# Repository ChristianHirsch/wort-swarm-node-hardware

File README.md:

# wort-swarm-node-hardware

This piece of hardware consists of a ICM-20948 9-axis inertial measurement unit (IMU), a Si705x digital temperature sensor, a nRF52840 system on chip (SoC) and battery management.

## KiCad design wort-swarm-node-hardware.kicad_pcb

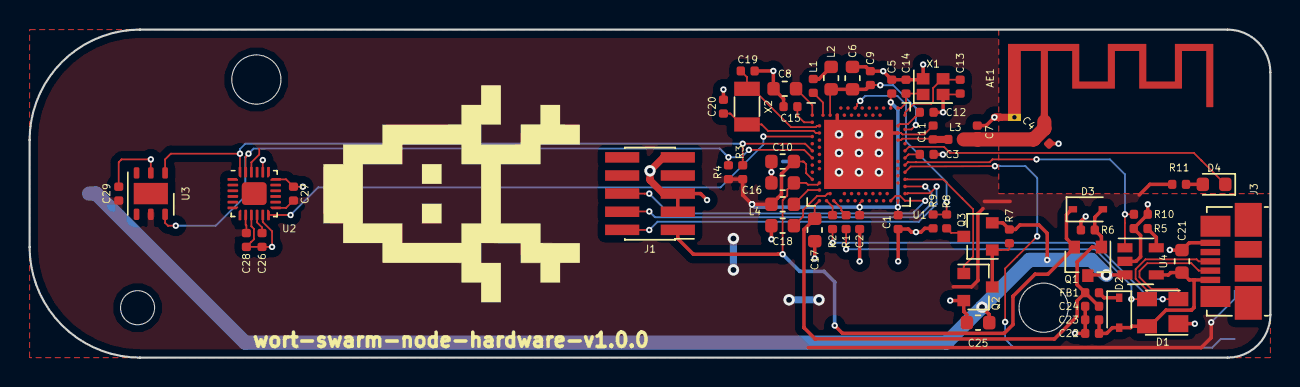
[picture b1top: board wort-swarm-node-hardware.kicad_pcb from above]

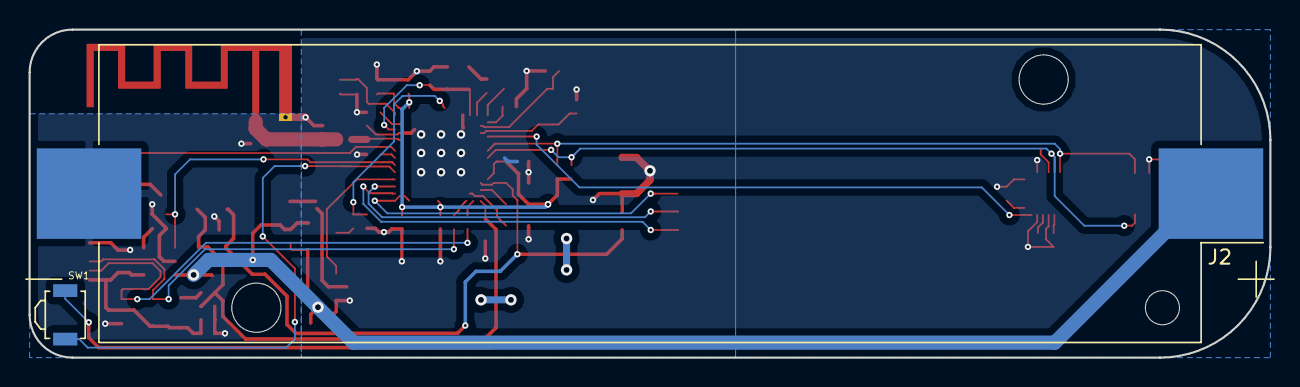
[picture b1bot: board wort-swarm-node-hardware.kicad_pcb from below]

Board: 2 copper layers, 87.0 x 23.0 mm, 63 parts (2 on the bottom side), 41 nets.

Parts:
AE1: Antenna_Shield; Texas_SWRA117D_2.4GHz_Right
C1, C2, C5, C15, C22, C24, C26, C27, C28, C29: 100n; C_0402_1005Metric
C3: 820p; C_0402_1005Metric
C4: N.C.; C_0402_1005Metric
C6, C8: 1u; C_0603_1608Metric
C7: 0.5p; C_0402_1005Metric
C9: 47n; C_0402_1005Metric
C10, C16, C17, C18, C25: 4.7u; C_0603_1608Metric
C11: 0.8p; C_0402_1005Metric
C12: 100p; C_0402_1005Metric
C13, C14, C19, C20: 12p; C_0402_1005Metric
C21: 10u; C_0603_1608Metric
C23: 10n; C_0402_1005Metric
D1: PRTR5V0U2X; SOT-143
D2, D3: BAT20J; D_SOD-323
D4: LED; LED_0603_1608Metric
FB1: 120R/0,55A; L_0402_1005Metric
J1: Conn_ARM_JTAG_SWD_10; PinHeader_2x05_P1.27mm_Vertical_SMD
J2: BATT_CONN; BatteryHolder_Keystone_1042_1x18650
J3: USB_B_Micro; USB_Micro-B_Molex_47346-0001
L1: 15n; L_0402_1005Metric
L2, L4: 10u; L_0603_1608Metric
L3: 3.9n, 5%; L_0402_1005Metric
Q1, Q3: DMP3099L-13; SOT-23
Q2: Q_NMOS_GSD; SOT-23
R1, R2: 0; R_0402_1005Metric
R3, R4, R6, R7, R10: 10k; R_0402_1005Metric
R5, R8: 3.3k; R_0402_1005Metric
R9: 8.2k; R_0402_1005Metric
R11: 220; R_0402_1005Metric
SW1: SW_Push; SW_SPST_B3U-3000P
U1: nRF52840; Nordic_AQFN-73-1EP_7x7mm_P0.5mm
U2: ICM-20948; QFN-24-1EP_3x3mm_P0.4mm_EP1.75x1.6mm
U3: Si7053-A20; DFN-6-1EP_3x3mm_P1mm_EP1.5x2.4mm
U4: MCP73812T-420I-OT; SOT-23-5
X1: 32MHz, 8pF; Crystal_SMD_2016-4Pin_2.0x1.6mm
X2: 32,768kHz, 9pF; Crystal_SMD_3215-2Pin_3.2x1.5mm

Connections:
+BATT: C25.1, J2.1, Q1.3, Q3.2, R7.1, U4.3
/ANT: C11.1, L3.2, U1.H23
/BATT_CHRG_EN: R10.1, U1.R24, U4.1
/BATT_V: R8.2, R9.1, U1.A12
/BATT_V_EN: Q2.1, U1.W24
/D+: R1.1, U1.AD6
/D-: R2.2, U1.AD4
/DCC: L1.1, U1.B3
/DCCH: L4.2, U1.AB2
/DEC1: C15.1, U1.C1
/DEC3: C12.1, U1.D23
/DEC4: C6.1, C9.1, L2.2, U1.B5, U1.E24
/DEC5: C3.1, U1.N24
/DECUSB: C18.1, U1.AC5
/ICM-20948_INT: U1.G1, U2.12
/LED: D4.1, U1.L24
/SCL: R4.2, U1.N1, U2.23, U3.6
/SDA: R3.2, U1.L1, U2.24, U3.1
/SWDCLK: J1.4, U1.AA24
/SWDIO: J1.2, U1.AC24
/SWO: J1.6, U1.AD22
/XC1: C13.2, U1.B24, X1.3
/XC2: C14.2, U1.A23, X1.1
/XL1: C19.2, U1.D2, X2.2
/XL2: C20.2, U1.F2, X2.1
/wort-swarm-node-hardware-components/V_USB: C21.1, C22.1, C23.1, D1.4, D2.2, J3.1, U4.4
GND: AE1.2, C1.2, C2.2, C3.2, C4.2, C5.2, C6.2, C7.2, C8.2, C9.2, C10.2, C11.2, C12.2, C13.1, C14.1, C15.2, C16.2, C17.2, C18.2, C19.1, C20.1, C21.2, C22.2, C23.2, C24.2, C25.2, C26.2, C27.2, C28.2, C29.2, D1.1, J1.3, J1.5, J1.9, J2.2, J3.5, Q2.2, R5.2, R6.1, R9.2, R10.2, U1.B7, U1.EP, U1.F23, U2.9, U2.11, U2.18, U2.20, U3.2, U4.2, X1.2, X1.4
LINE: C16.1, D3.1, J1.1, Q1.2, U1.Y2
unnamed: AE1.1, C4.1, C7.1, L3.1
unnamed: C26.1, U2.10
unnamed: D1.2, J3.2, R2.1
unnamed: D1.3, J3.3, R1.2
unnamed: D2.1, FB1.2
unnamed: D4.2, R11.2
unnamed: L1.2, L2.1
unnamed: Q2.3, Q3.1, R7.2
unnamed: Q3.3, R8.1
unnamed: R5.1, U4.5
unnamed: SW1.1, U1.U24
VBUS: C17.1, C24.1, D3.2, FB1.1, Q1.1, R6.2, U1.AD2
VCC: C1.1, C2.1, C5.1, C8.1, C10.1, C27.1, C28.1, C29.1, L4.1, R3.1, R4.1, R11.1, SW1.2, U1.A22, U1.AD14, U1.AD23, U1.B1, U1.W1, U2.8, U2.13, U2.22, U3.5
